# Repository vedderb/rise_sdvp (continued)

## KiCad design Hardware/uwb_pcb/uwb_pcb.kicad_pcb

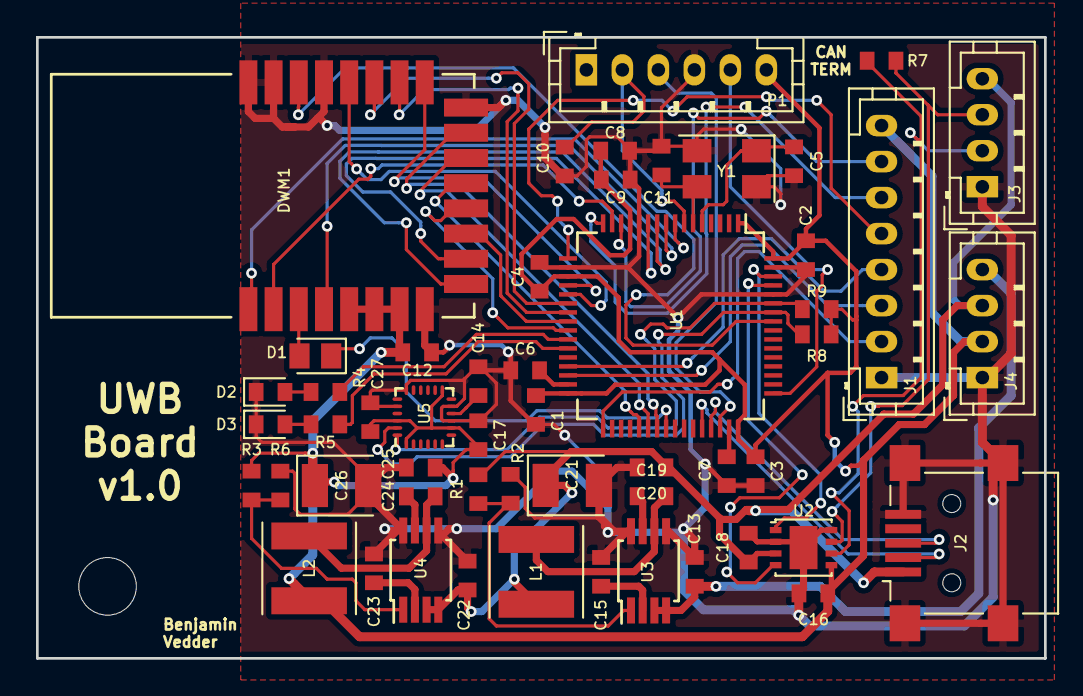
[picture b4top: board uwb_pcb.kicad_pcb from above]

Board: 2 copper layers, 56.0 x 34.5 mm, 54 parts (0 on the bottom side), 55 nets.

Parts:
C1, C2, C3, C4, C6, C7, C8, C9, C12, C13, C15, C16, C17, C18, C20, C22, C23, C25, C27: 2.2u; C_0603_1608Metric
C5, C11: 15p; C_0603_1608Metric
C10, C14, C19, C24: 100n; C_0603_1608Metric
C21, C26: 100u; CP_EIA-3528-12_Kemet-T
D1: D_Schottky; D_0805_2012Metric
D2: RED; LED_0603_1608Metric
D3: GREEN; LED_0603_1608Metric
DWM1: DWM1000
J1: COMM; JST_PH_B8B-PH-K_1x08_P2.00mm_Vertical
J2: USB_B_Mini; USB_Mini-B_Lumberg_2486_01_Horizontal
J3: CAN; JST_PH_B4B-PH-K_1x04_P2.00mm_Vertical
J4: PWR; JST_PH_B4B-PH-K_1x04_P2.00mm_Vertical
L1, L2: 22U; L_Taiyo-Yuden_MD-5050
MK1: Mounting_Hole; MountingHole_3.2mm_M3
P1: SWD; JST_PH_B6B-PH-K_1x06_P2.00mm_Vertical
R1: 52.3k; R_0603_1608Metric
R2, R6: 10k; R_0603_1608Metric
R3: 33k; R_0603_1608Metric
R4, R5, R8, R9: 1k; R_0603_1608Metric
R7: 220R; R_0603_1608Metric
U1: STM32F40X_LQFP64; LQFP-64_10x10mm_P0.5mm
U2: TJA1051TK-3; DFN-8-1EP_3x3mm_P0.65mm_EP1.55x2.4mm
U3, U4: MCP16311/2; MSOP-8_3x3mm_P0.65mm
U5: MPU9250; QFN-24-1EP_3x3mm_P0.4mm_nopp
Y1: 8M; Crystal_SMD_5032-4Pin_5.0x3.2mm

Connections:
5V: C18.1, C20.1, C21.1, C22.1, J2.1, J3.4, J4.3, L1.1, R1.2, U2.3, U4.3, U4.4
CANH: J3.3, R7.2, U2.7
CANL: J3.2, R7.1, U2.6
CAN_RX: U1.61, U2.4
CAN_TX: U1.62, U2.1
DW_CLK: DWM1.20, U1.21
DW_CS: DWM1.17, U1.20
DW_EXTON: DWM1.1, U1.8
DW_GPIO0: DWM1.15, U1.39
DW_GPIO1: DWM1.14, U1.38
DW_GPIO2: DWM1.13, U1.37
DW_GPIO3: DWM1.12, U1.25
DW_GPIO4: DWM1.11, U1.24
DW_GPIO5: DWM1.10, U1.11
DW_GPIO6: DWM1.9, U1.10
DW_GPIO7: DWM1.4, U1.9
DW_IRQ: DWM1.22, U1.57
DW_MISO: DWM1.19, U1.22
DW_MOSI: DWM1.18, U1.23
DW_RST: D1.1, U1.40
DW_WAKEUP: DWM1.2, U1.15
GND: C1.2, C2.2, C3.2, C4.2, C5.1, C6.1, C7.1, C8.2, C9.2, C10.2, C11.1, C12.2, C13.2, C14.2, C15.2, C16.2, C17.2, C18.2, C20.2, C21.2, C22.2, C23.2, C25.2, C26.2, C27.2, D2.1, D3.1, DWM1.8, DWM1.16, DWM1.21, DWM1.23, DWM1.24, J1.1, J2.5, J2.6, J3.1, J4.1, P1.4, R2.1, R6.1, U1.12, U1.18, U1.60, U1.63, U2.2, U2.8, U2.9, U3.5, U3.8, U4.5, U4.8, U5.9, U5.11, U5.18, U5.20, Y1.2, Y1.4
LED_GREEN: R4.1, U1.26
LED_RED: R5.1, U1.27
NRST: C10.1, P1.2, U1.7
unnamed: C5.2, U1.5, Y1.1
unnamed: C6.2, U1.31
unnamed: C7.2, U1.47
unnamed: C11.2, U1.6, Y1.3
unnamed: C14.1, U5.10
unnamed: C15.1, U3.2
unnamed: C19.1, U3.7
unnamed: C19.2, L1.2, U3.6
unnamed: C23.1, U4.2
unnamed: C24.1, U4.7
unnamed: C24.2, L2.2, U4.6
unnamed: D1.2, DWM1.3
unnamed: D2.2, R4.2
unnamed: D3.2, R5.2
unnamed: R1.1, R2.2, U3.1
unnamed: R3.1, R6.2, U4.1
PA0: J1.7, U1.14
PA2: J1.6, U1.16
PA3: J1.5, U1.17
PB10: J1.4, U1.29
PB11: J1.3, U1.30
PB12: J1.2, U1.33
SCL: R8.1, U1.58, U5.23
SDA: R9.1, U1.59, U5.24
SWCLK: P1.5, U1.49
SWDIO: P1.3, U1.46
USB_DM: J2.2, U1.44
USB_DP: J2.3, U1.45
VCC: C1.1, C2.1, C3.1, C4.1, C8.1, C9.1, C12.1, C16.1, C17.1, C25.1, C26.1, C27.1, DWM1.5, DWM1.6, DWM1.7, J1.8, J4.2, L2.1, P1.6, R3.2, R8.2, R9.2, U1.1, U1.13, U1.19, U1.32, U1.48, U1.64, U2.5, U5.1, U5.8, U5.13, U5.22
V_IN: C13.1, J4.4, U3.3, U3.4

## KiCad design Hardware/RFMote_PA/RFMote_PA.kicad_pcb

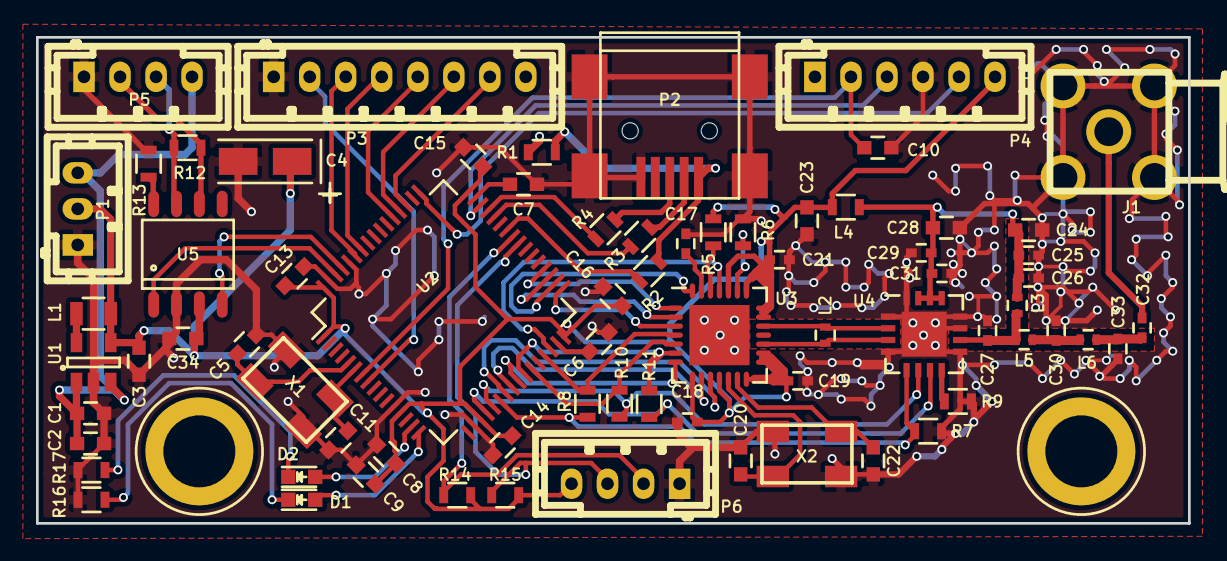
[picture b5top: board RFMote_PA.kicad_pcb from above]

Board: 4 copper layers, 64.0 x 27.0 mm, 74 parts (0 on the bottom side), 61 nets.

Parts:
1PIN, 1PIN#2: P***; 1pin_4mm
C1, C2, C3, C6, C7, C8, C9, C13, C14, C15, C16, C23, C24, C28, C34: 2.2u; C_0603
C4: 100u; TantalC_SizeA_EIA-3216_Wave
C5, C11, C20, C22: 15p; C_0603
C10: 100n; C_0603
C17, C18, C19, C21: 100n; C_0402
C25, C29: 1n; C_0402
C26, C31: 12p; C_0402
C27, C30: 2.2p; C_0402
C32: 18p; C_0402
C33: 0.2p; C_0402
D1: RED; LED-0603
D2: GREEN; LED-0603
J1: SMA; sma_90_crf
L1: 2.2u; R_0805
L2: DNM; R_0402
L3: 4.7n; R_0402
L4: BEAD; R_0603
L5: 1n; R_0402
L6: 2n; R_0402
P1: V_IN; b3b-ph-kl
P2: USB_OTG; USB_Mini-B
P3: COMM; b8b-ph-kl
P4: SWD; b6b-ph-kl
P5: CAN; b4b-ph-kl
P6: I2C; b4b-ph-kl
R1: 0R; R_0603
R2, R3, R4: 22R; R_0603
R5, R8, R10, R11, R13: 10k; R_0603
R6, R7: 56k; R_0603
R9: 3.9k; R_0603
R12: 220R; R_0603
R14, R15, R16, R17: 1k; R_0603
U1: LM3671; SOT-23-5
U2: STM32F40X_LQFP64; LQFP-64_10x10mm_Pitch0.5mm
U3: CC2520; QFN-28-1EP_5x5mm_Pitch0.5mm
U4: CC2592; QFN-16-1EP_4x4mm_Pitch0.65mm
U5: MCP2551-I/SN; SO-8
X1: 8m; Crystal_5x3mm_3pin
X2: 32M; Crystal_5x3mm_3pin

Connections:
+5V: C1.1, C2.1, P1.3, P5.4, R1.2, U1.1, U1.3
/CAN/CANH: P5.3, R12.1, U5.7
/CAN/CANL: P5.2, R12.2, U5.6
/CAN/CAN_RX: U2.61, U5.4
/CAN/CAN_TX: U2.62, U5.1
/CC2520/CC_CS_N: U2.33, U3.3
/CC2520/CC_GPIO0: U2.23, U3.10
/CC2520/CC_GPIO1: U2.24, U3.9
/CC2520/CC_GPIO2: U2.25, U3.7
/CC2520/CC_GPIO3: R11.1, U2.26, U3.6
/CC2520/CC_GPIO4: R10.1, U2.27, U3.5
/CC2520/CC_GPIO5: R8.1, U2.29, U3.4
/CC2520/CC_RESET: U2.30, U3.25
/CC2520/CC_SCLK: U2.34, U3.28
/CC2520/CC_SI: U2.35, U3.2
/CC2520/CC_SO: U2.36, U3.1
/CC2520/HGM: R11.2, U2.20, U4.7
/CC2520/LNA_EN: R10.2, U2.21, U4.6
/CC2520/VDD_CC2592: C24.2, C25.2, C26.2, C28.2, C29.2, C31.2, L3.2, L4.2, U4.13, U4.14, U4.15
/MCU/NRST: C10.1, P4.2, U2.7
/MCU/PA1: D2.2, U2.15
/MCU/PA2: D1.2, U2.16
/MCU/PA6: R7.1, R8.2, U2.22, U4.5
/MCU/PA8_SCL3: P6.2, R14.1, U2.41
/MCU/PB6_SCL1: P3.4, U2.58
/MCU/PB7_SDA1: P3.3, U2.59
/MCU/PC0_ADC10: P3.2, U2.8
/MCU/PC9_SDA3: P6.3, R15.1, U2.40
/MCU/PC10_SCK3_TX3: P3.7, U2.51
/MCU/PC11_MISO3_RX3: P3.6, U2.52
/MCU/PC12_MOSI3: P3.5, U2.53
/MCU/SWCLK: P4.5, U2.49
/MCU/SWDIO: P4.3, U2.46
/MCU/USB_DM: R3.1, U2.44
/MCU/USB_DP: R4.1, U2.45
/MCU/USB_VBUS: R2.1, U2.42
GND: C1.2, C2.2, C3.2, C4.2, C5.1, C6.1, C7.1, C8.2, C9.2, C10.2, C11.1, C13.2, C14.2, C15.2, C16.2, C17.1, C18.1, C19.1, C20.2, C21.1, C22.2, C23.1, C24.1, C25.1, C26.1, C27.1, C28.1, C29.1, C30.1, C31.1, C33.1, C34.2, J1.2, P1.1, P2.5, P2.6, P3.1, P4.4, P5.1, P6.1, R6.2, R7.2, R9.2, R13.2, R16.2, R17.2, U1.2, U2.12, U2.18, U2.60, U2.63, U3.29, U4.1, U4.4, U4.9, U4.11, U4.12, U4.16, U4.17, U5.2, X1.3, X2.3
unnamed: C5.2, U2.5, X1.1
unnamed: C6.2, U2.31
unnamed: C7.2, U2.47
unnamed: C11.2, U2.6, X1.2
unnamed: C17.2, U3.27
unnamed: C20.1, U3.12, X2.1
unnamed: C22.1, U3.13, X2.2
unnamed: C27.2, L3.1, L5.1, U4.10
unnamed: C30.2, L5.2, L6.1
unnamed: C32.1, C33.2, L6.2
unnamed: C32.2, J1.1
unnamed: D1.1, R16.1
unnamed: D2.1, R17.1
unnamed: L1.1, U1.5
unnamed: L2.1, U3.19, U4.2
unnamed: L2.2, U3.17, U4.3
unnamed: P2.1, R1.1, R2.2
unnamed: P2.2, R3.2
unnamed: P2.3, R4.2
unnamed: R5.2, U3.26
unnamed: R6.1, U3.23
unnamed: R9.1, U4.8
unnamed: R13.1, U5.8
VCC: C3.1, C4.1, C8.1, C9.1, C13.1, C14.1, C15.1, C16.1, C18.2, C19.2, C21.2, C23.2, C34.1, L1.2, L4.1, P1.2, P3.8, P4.6, P6.4, R5.1, R14.2, R15.2, U1.4, U2.1, U2.13, U2.19, U2.32, U2.48, U2.64, U3.8, U3.11, U3.14, U3.15, U3.16, U3.20, U3.21, U3.22, U3.24, U5.3

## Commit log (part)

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2018-11-26 Added missing file
2018-12-04 Simulator updates
2018-12-16 Make simulated cars work with the scala tests
2018-12-29 Added micronav joystick support
2019-01-02 Camera support fixes
2019-01-02 Added fullscreen mode to RControlStation
2019-01-03 F11 for fullscreen, more camera info
2019-01-03 Added fullscreen camera support and support for some joystick buttons
2019-01-07 Camera frame dropping, store traces without map in focus, interaction mode in mapwidget, arrows to emulate scroll in mapwidget, better Car_Client id handling
2019-01-07 Added more micronav support
2019-01-18 Changed OrientationWidget to QOpenGLWidget
2019-01-23 Initial SimScen support
2019-01-23 More SimScen updates
2019-01-23 SimScen open scenario bug fix
2019-01-23 Restore painter after map module painting
2019-02-13 Chronos updates
2019-02-15 Added android release rules
2019-02-17 Added android build settings
2019-02-18 Removed AP radius from simscen cars
2019-02-20 Some plotting improvements
2019-02-22 Added fault injection to simulator
2019-02-22 FI fix
2019-03-06 more chronos updates
2019-03-20 FW ap fix
2019-03-28 Added log command to list uwb anchors, use same tcp server for logging from simulated cars
2019-03-28 Updated car log message
2019-04-01 Added build files to gitignore
2019-04-04 Added VESC servo, hydraulic drive and drangen support
2019-04-05 VESC Servo and hydraulic updates
2019-04-05 Added hydraulic safety timeout and decreased servo frequency
2019-04-09 More usage of chronos sender ID
2019-04-16 Update README.md
    More added
2019-04-16 Update README.md
    Added Qt creator cross compile setup guide
2019-04-16 Added scripts for cross compilation, removed camera support from car client
2019-04-16 Update README.md
    Small changes
2019-04-25 Added install deployment target and added GUI define
2019-04-25 Added font includements
2019-04-25 Modified qml to handle EGLFS
2019-05-07 Major documentation update
2019-05-09 Added more logging functions to scala_test
2019-05-13 Octave experiment plotting
2019-05-13 Added zoom in on route function
2019-05-17 Fixed bug when reading routes
2019-05-20 Added command line arguments to plot routes from RControlStation
2019-05-21 Added support for multiple TCP connections and new command line arguments
2019-05-28 Added cli parameter to set chronos transmitter id
2019-06-25 Added reset script for raspberry pi
2019-07-04 Added scatterplot button for experiment plot
2019-07-04 Removed unused include
2019-07-29 Added TRCM, ACCM, TREO, EXAC and CATA messages to chronoscom.h
2019-07-29 Parsed ACCM and EXAC
2019-07-29 fixed spelling errors and added TODO comments
2019-08-02 Added basic pinOut things
2019-08-02 Added GPIO control using sysfs
2019-08-05 Updated ChronosComm to unsetPin on close connection
2019-08-08 Added #define for pin
2019-08-08 Moved PIN defines and other defines to gpio.cpp
2019-08-08 Moved setting of GPIO to ACCM
2019-08-08 Created dev branch
2019-08-09 Added printotus on succes
2019-08-12 Added typedef for pin operations
2019-08-12 Fixed wrong pin setting
2019-08-14 Rebuilt FWs
2019-08-15 Updated simscen in RControlStation project file
2019-08-16 Updated Car_Client
2019-08-16 UWB Fixes
2019-08-21 Starting the car-tcp-server (for rcontrolstation interfacing) at the same address as the chronos tcp serverif in mode Chronos and using a custom network interface
2019-09-02 Added TREO parsing
2019-09-03 Removed TREO handling in chronoscom
2019-09-03 Added base station support to GPS sim
2019-09-10 adding plots and data related to the Automated testing paper
2019-09-12 FW check, added route point attributes, new AP radius calculation
2019-09-19 Change monr message to match with ISO spec
2019-09-23 Moving development of the f9p board to rise_sdvp repository
2019-09-23 added readme
2019-09-24 F9P_Board : ERC without complaints. Wiring most things up. Need review
2019-09-24 F9P_Board experimenting with how to lay components out
2019-09-25 Updated UWB case
2019-09-26 Added missing break in monr decode
2019-09-26 f9p_board: started to route and some some small rearrangements
2019-09-28 Added uwb pcb case gcode that is easier to print
2019-10-02 Some updates on F9P board
2019-10-02 setting car transmitter id from opro message to objects
2019-10-03 Initialize state in motor sim
2019-10-03 Fixed opro connection
2019-10-06 rearranged all the components to align with the grid
2019-10-07 Improvements
2019-10-07 updating component footprints for inductor and caps on dcdc part
2019-10-08 started routing
2019-10-10 f9p_board: progress with routing
2019-10-11 f9p_board: connecting CAN 5v to PWR_5V net. Also everything routed - first attempt
2019-10-13 f9p_board: routing
2019-10-14 Finished F9P PCB v1.0
2019-10-17 Fixed merge conflicts
2019-10-22 f9p_board: adding more Order numbers
2019-10-22 RControlSttation.pro do not build with limesdr as default
2019-11-06 f9p_board added lots of ordernr from digikey and a stp file for rf connector
2019-11-06 Do not allow multiple anchors with the same id
2019-11-06 Added ping and reset functions to UWB module
2019-11-08 Added uptime command to UWB module
2019-11-08 Fixed UWB pcb watchdog and added twostep SSH tunnel example script
2019-11-08 Increased stop break current and uncheck poll and kb control when starting camera stream
2019-11-12 Removed old gerber files
2019-11-12 Display more RTCM messages and do not re-encode RTCM
2019-11-13 F9P base station support and more features
2019-11-19 added 3.3V can
2019-11-20 Added galileo support to base station
2019-11-20 Compiled FWs
2019-11-21 Added terminal command buttons
2019-11-21 Added UWB max corr parameter
2019-11-25 Use QCoreApplication instead of QApplication in Car_Client when the --usegui argument is not passed
2019-11-25 Added SWD support for raspberry pi 4
2019-11-25 Updated fw upload help text
2019-11-26 Added terminal command to read input voltage
2019-11-26 Recompiled FWs
2019-11-26 Added support to update car id from Car_Client
2019-12-11 uping FW version of Carsim and adding the OPRO-TO-CAR message processing to Chronoscomm
2020-01-14 moving a resistor that was very close to the power connector
2020-01-14 Moved another resistor a bit. please check my work for sanity
2020-01-15 commented out some unused code in routemagic
2020-01-15 Do not activate LimeSDR per default
2020-01-16 added filering of the very dense trajectories generated by the space filler
2020-01-24 testing to commit to RISE organization
2020-01-26 Disable timeout braking below 2 km/h
2020-02-03 Added IO board
2020-02-03 added some text to the IO board
2020-02-05 experimenting with polygong-filling-routes
2020-03-04 RouteMagic: first version of fillConvexPolygonWithZigZag
2020-03-05 RouteMagic: new approach to keep distance to outer bounds when generating zigzag (1. resize bounds, 2. generate)
2020-03-09 Updated MONR struct content length and value ID
2020-03-18 RouteMagic: some cleanups
2020-03-18 implement RouteMagic::fillConvexPolygonWithFramedZigZag, update UI
2020-03-19 RouteMagic::fillConvexPolygonWithZigZag: implement smooth turns
2020-03-20 RouteMagic::fillConvexPolygonWithZigZag: guarantee that turns stay within bounds
2020-04-01 RouteMagic::fillConvexPolygonWithFramedZigZag: introduce additional points for predictable processing of attributes, introduce attributes_masks.h, UI updates
2020-04-05 Added valve connector photo
2020-04-05 Added IO board test commands and slider
2020-04-11 Initial mactrac support
2020-04-13 Ublox fixes for new FW, mactrac hydraulic actuator support
2020-04-13 Updated ublox relposned msg decode, added mactrac limitsw support
2020-04-13 Fixed antenna offset calculation
2020-04-13 Implemented mactrac speed sensor
2020-04-17 Mactrac updates
2020-04-22 fillConvexPolygonWithZigZag: set attributes on straights (front hydr. down) and turns (front hydr. up), visualize in map view
2020-04-22 autopilot: actuate hydraulics based on attributes
2020-05-05 fillConvexPolygonWithZigZag: visit every xth line impelemented for even x (going back to origin after every pass)
2020-05-06 Route Generation: UI cleanup
2020-05-11 fix windows build (add Opengl32 lib)
2020-05-13 RC_Controller: Add vehicle-specific targets to Makefile
2020-05-20 RC_Controller: fix setting UART1 baudrate on unconfigured F9P chips
2020-05-25 RControlStation/rtcmwidget: fix typo
2020-05-28 RControlStation/ublox: add TODO about UBX_NAV_SOL (was dropped on F9P)
2020-05-28 RControlStation: do not configure UART1 when connecting UBX over USB
2020-05-28 RControlStation: disable debug output in release build
2020-05-28 RControlStation/task_basestation: implement commandline parameters
2020-05-28 RControlStation: implement "task_basestation" a command line mode of RControlStation that serves as a RTK GNSS basestation after survey-in, sending RTCM3 over TCP (based on basestation functionality 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
    RControlStation: implement rxSvin slot in Task_BaseStation
    RControlStation: implement Task_BaseStation::rtcmRx
    RControlStation/Task_BaseStation: implement rxNavSat, console status output
    RControlStation/task_basestation: print more info, format output
2020-05-28 RControlStation: refactor BaseStation::on_ubxSerialConnectButton_clicked() such that UBX configuration becomes a static function
2020-06-02 RControlStation/Task_BaseStation: show internal IP(s) as well
2020-06-17 RC_Controller: add mactrac target, add download_fw script
2020-06-17 RC_Controller: add precompiled MacTrac firmware
2020-06-17 RControlStation: clarify wireguard status description
2020-06-17 RC_Controller: add default debug launch file for MCU Eclipse
2020-06-17 RC_Controller/Makefile: keep *.elf for debugging
2020-06-17 RC_Controller: upgrade ChibiOS from 3.0.2 to 3.0.5 (final 3.x version)
2020-06-17 RControlStation/task_basestation: fix local IP output
2020-07-11 Reset m_point_now in autopilot when reaching end of route
2020-07-11 Disable repeat routes by default on mactrac
2020-07-14 RControlStation: enable using PS3/PS4 controller as multirotor joystick
2020-09-24 Added TRANSMITTER_ID value id
2020-09-24 Small fix
2020-09-24 Changing osem in chronoscom
2020-09-24 Added some basic defines and stuff
2020-09-25 Added qt connections for OPROrx
2020-09-28 Remoced bitshift
2020-09-28 Fixes
2020-09-29 Temp remocve checksum to see debug prints
2020-09-29 Another debug print
2020-09-29 Debug prints parsing OSEM
2020-09-30 Value ID debug print
2020-09-30 Added sendOPRO
2020-09-30 Update Linux/Car_Client/chronoscomm.cpp
    Removed Debug OSEM print
2020-10-01 Added last osem parts
2020-10-01 Now uses standard ISO value IDs
2020-10-01 added some OPRO values
2020-10-02 Sending OPRO after OSEM rx
2020-10-05 Removed extra sendOpro
2020-10-05 Fixed content ordering bös
2020-10-16 RControlStation: send periodic (300ms) heartbeat to vehicles
2020-10-16 RControlStationComm/mavlink_followrcs: version tested with rc vehicles (wip)
2020-10-16 RControlStationComm/mavlink_followrcs: some fine-tuning
2020-10-16 RControlStation: send heartbeat only if firmware version major > 20
2020-10-21 autopilot (RC_Controller, Car_Client, RControlStation): always start route from beginning, extended control interface to (re)start/pause/stop autopilot
    RC_Controller/autopilot: make sure attributes are ignored until route is followed
2020-10-22 RControlStation: highlight first and last point in active route
2020-10-23 RControlStation/wireguard: set default values for uppsala basestation
2020-10-28 RControlStation: separate parameters for raising/lowering tool distance when generating routes
2020-10-29 RControlStation/routemagic: fix broken turns in specific case
2020-11-09 RControlStation: set F9P as default in basestation, send basestation postition by default
2020-11-16 RControlStation/rtcmwidget: update default port and stream name (Borås)
2020-11-20 RControlStation/Basestation: introduce moving basestation feature (note: measurement rate on base and rover need to be identical, high latencies like over 4G can be problematic)
2020-12-26 Updated openSCENARIO parser to reflect changes in file format
2021-03-03 Added very basic and limited initial support for RCMM.
